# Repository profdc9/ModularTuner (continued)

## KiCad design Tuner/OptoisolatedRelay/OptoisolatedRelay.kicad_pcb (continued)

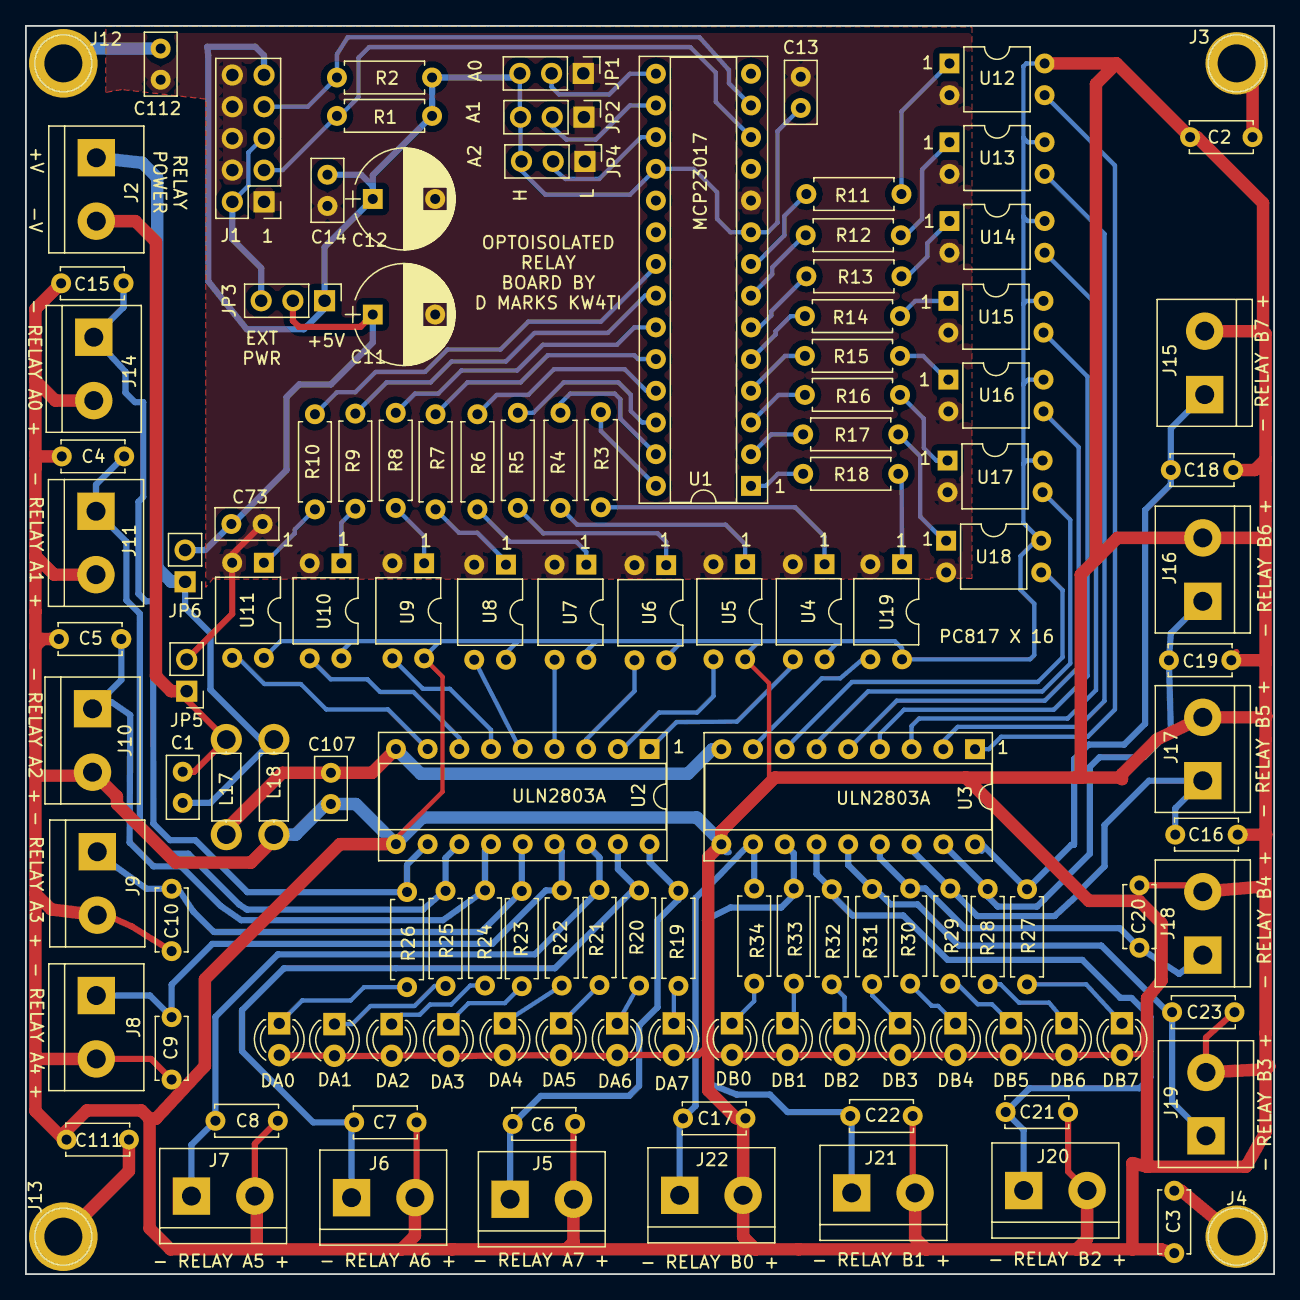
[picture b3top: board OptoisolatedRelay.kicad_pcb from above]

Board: 2 copper layers, 100.0 x 100.0 mm, 126 parts (0 on the bottom side), 97 nets.

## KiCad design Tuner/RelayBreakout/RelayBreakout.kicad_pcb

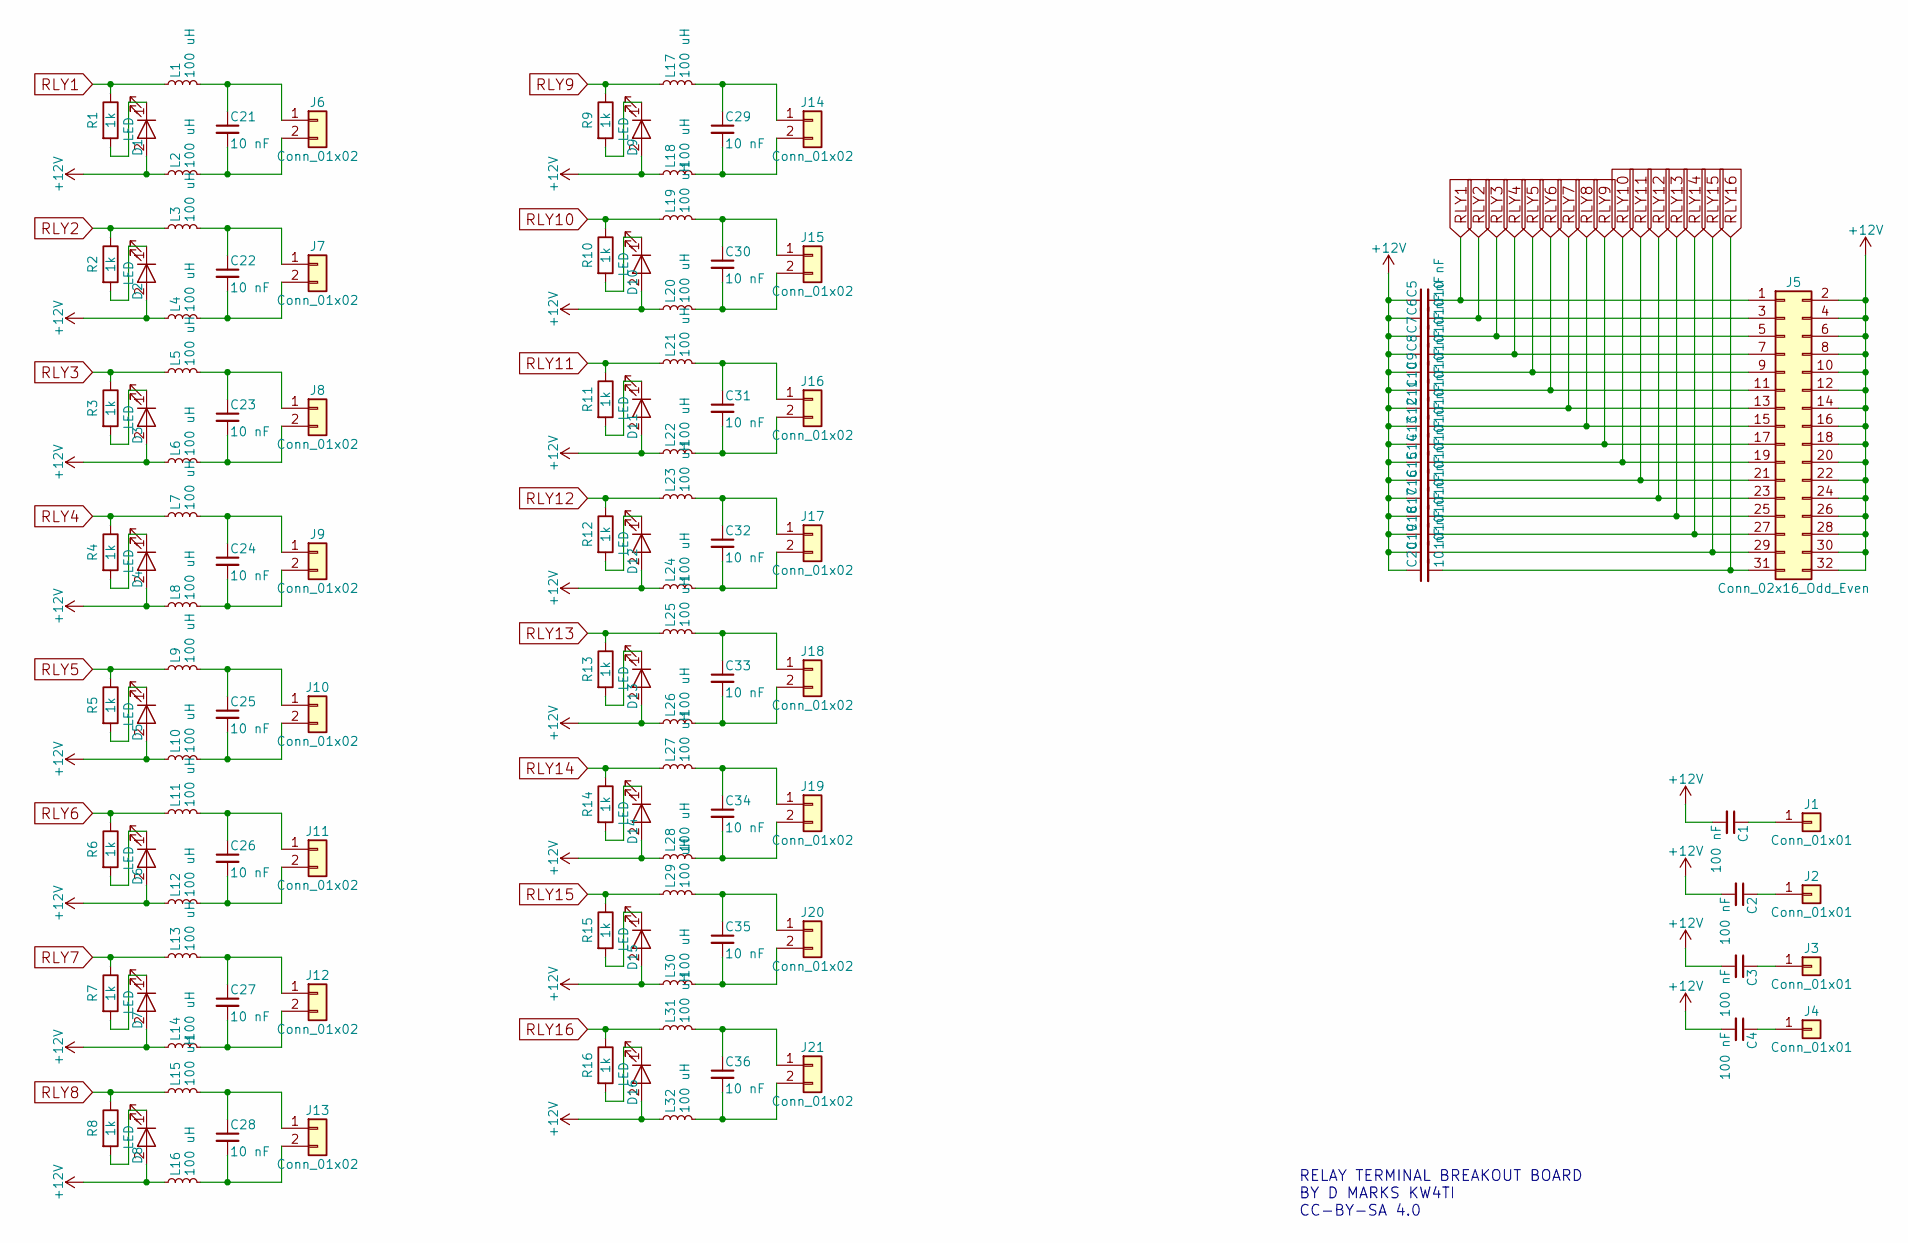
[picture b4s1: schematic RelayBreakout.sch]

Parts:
C1, C2, C3, C4: 100 nF; C_Disc_D5.0mm_W2.5mm_P5.00mm
C5, C6, C7, C8, C9, C10, C11, C12, C13, C14, C15, C16, C17, C18, C19, C20, C21, C22, C23, C24, C25, C26, C27, C28, C29, C30, C31, C32, C33, C34, C35, C36: 10 nF; C_Disc_D5.0mm_W2.5mm_P2.50mm
D1, D2, D3, D4, D5, D6, D7, D8, D9, D10, D11, D12, D13, D14, D15, D16: LED; LED_D3.0mm
J1, J2, J3, J4: Conn_01x01; 1pin
J5: Conn_02x16_Odd_Even; Pin_Header_Straight_2x16_Pitch2.54mm
J6, J7, J8, J9, J10, J11, J12, J13, J14, J15, J16, J17, J18, J19, J20, J21: Conn_01x02; TerminalBlock_bornier-2_P5.08mm
L1, L2, L3, L4, L5, L6, L7, L8, L9, L10, L11, L12, L13, L14, L15, L16, L17, L18, L19, L20, L21, L22, L23, L24, L25, L26, L27, L28, L29, L30, L31, L32: 100 uH; L_Axial_L5.3mm_D2.2mm_P7.62mm_Horizontal_Vishay_IM-1
R1, R2, R3, R4, R5, R6, R7, R8, R9, R10, R11, R12, R13, R14, R15, R16: 1k; R_Axial_DIN0207_L6.3mm_D2.5mm_P7.62mm_Horizontal

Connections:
+12V: C1.2, C2.2, C3.2, C4.2, C5.1, C6.1, C7.1, C8.1, C9.1, C10.1, C11.1, C12.1, C13.1, C14.1, C15.1, C16.1, C17.1, C18.1, C19.1, C20.1, D1.2 (A), D2.2 (A), D3.2 (A), D4.2 (A), D5.2 (A), D6.2 (A), D7.2 (A), D8.2 (A), D9.2 (A), D10.2 (A), D11.2 (A), D12.2 (A), D13.2 (A), D14.2 (A), D15.2 (A), D16.2 (A), J5.2, J5.4, J5.6, J5.8, J5.10, J5.12, J5.14, J5.16, J5.18, J5.20, J5.22, J5.24, J5.26, J5.28, J5.30, J5.32, L2.1, L4.1, L6.1, L8.1, L10.1, L12.1, L14.1, L16.1, L18.1, L20.1, L22.1, L24.1, L26.1, L28.1, L30.1, L32.1
unnamed: C1.1, J1.1
unnamed: C2.1, J2.1
unnamed: C3.1, J3.1
unnamed: C4.1, J4.1
unnamed: C21.1, J6.1, L1.2
unnamed: C21.2, J6.2, L2.2
unnamed: C22.1, J7.1, L3.2
unnamed: C22.2, J7.2, L4.2
unnamed: C23.1, J8.1, L5.2
unnamed: C23.2, J8.2, L6.2
unnamed: C24.1, J9.1, L7.2
unnamed: C24.2, J9.2, L8.2
unnamed: C25.1, J10.1, L9.2
unnamed: C25.2, J10.2, L10.2
unnamed: C26.1, J11.1, L11.2
unnamed: C26.2, J11.2, L12.2
unnamed: C27.1, J12.1, L13.2
unnamed: C27.2, J12.2, L14.2
unnamed: C28.1, J13.1, L15.2
unnamed: C28.2, J13.2, L16.2
unnamed: C29.1, J14.1, L17.2
unnamed: C29.2, J14.2, L18.2
unnamed: C30.1, J15.1, L19.2
unnamed: C30.2, J15.2, L20.2
unnamed: C31.1, J16.1, L21.2
unnamed: C31.2, J16.2, L22.2
unnamed: C32.1, J17.1, L23.2
unnamed: C32.2, J17.2, L24.2
unnamed: C33.1, J18.1, L25.2
unnamed: C33.2, J18.2, L26.2
unnamed: C34.1, J19.1, L27.2
unnamed: C34.2, J19.2, L28.2
unnamed: C35.1, J20.1, L29.2
unnamed: C35.2, J20.2, L30.2
unnamed: C36.1, J21.1, L31.2
unnamed: C36.2, J21.2, L32.2
unnamed: D1.1 (K), R1.2
unnamed: D2.1 (K), R2.2
unnamed: D3.1 (K), R3.2
unnamed: D4.1 (K), R4.2
unnamed: D5.1 (K), R5.2
unnamed: D6.1 (K), R6.2
unnamed: D7.1 (K), R7.2
unnamed: D8.1 (K), R8.2
unnamed: D9.1 (K), R9.2
unnamed: D10.1 (K), R10.2
unnamed: D11.1 (K), R11.2
unnamed: D12.1 (K), R12.2
unnamed: D13.1 (K), R13.2
unnamed: D14.1 (K), R14.2
unnamed: D15.1 (K), R15.2
unnamed: D16.1 (K), R16.2
RLY1: C5.2, J5.1, L1.1, R1.1
RLY2: C6.2, J5.3, L3.1, R2.1
RLY3: C7.2, J5.5, L5.1, R3.1
RLY4: C8.2, J5.7, L7.1, R4.1
RLY5: C9.2, J5.9, L9.1, R5.1
RLY6: C10.2, J5.11, L11.1, R6.1
RLY7: C11.2, J5.13, L13.1, R7.1
RLY8: C12.2, J5.15, L15.1, R8.1
RLY9: C13.2, J5.17, L17.1, R9.1
RLY10: C14.2, J5.19, L19.1, R10.1
RLY11: C15.2, J5.21, L21.1, R11.1
RLY12: C16.2, J5.23, L23.1, R12.1
RLY13: C17.2, J5.25, L25.1, R13.1
RLY14: C18.2, J5.27, L27.1, R14.1
RLY15: C19.2, J5.29, L29.1, R15.1
RLY16: C20.2, J5.31, L31.1, R16.1

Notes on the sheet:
RELAY TERMINAL BREAKOUT BOARD BY D MARKS KW4TI CC-BY-SA 4.0

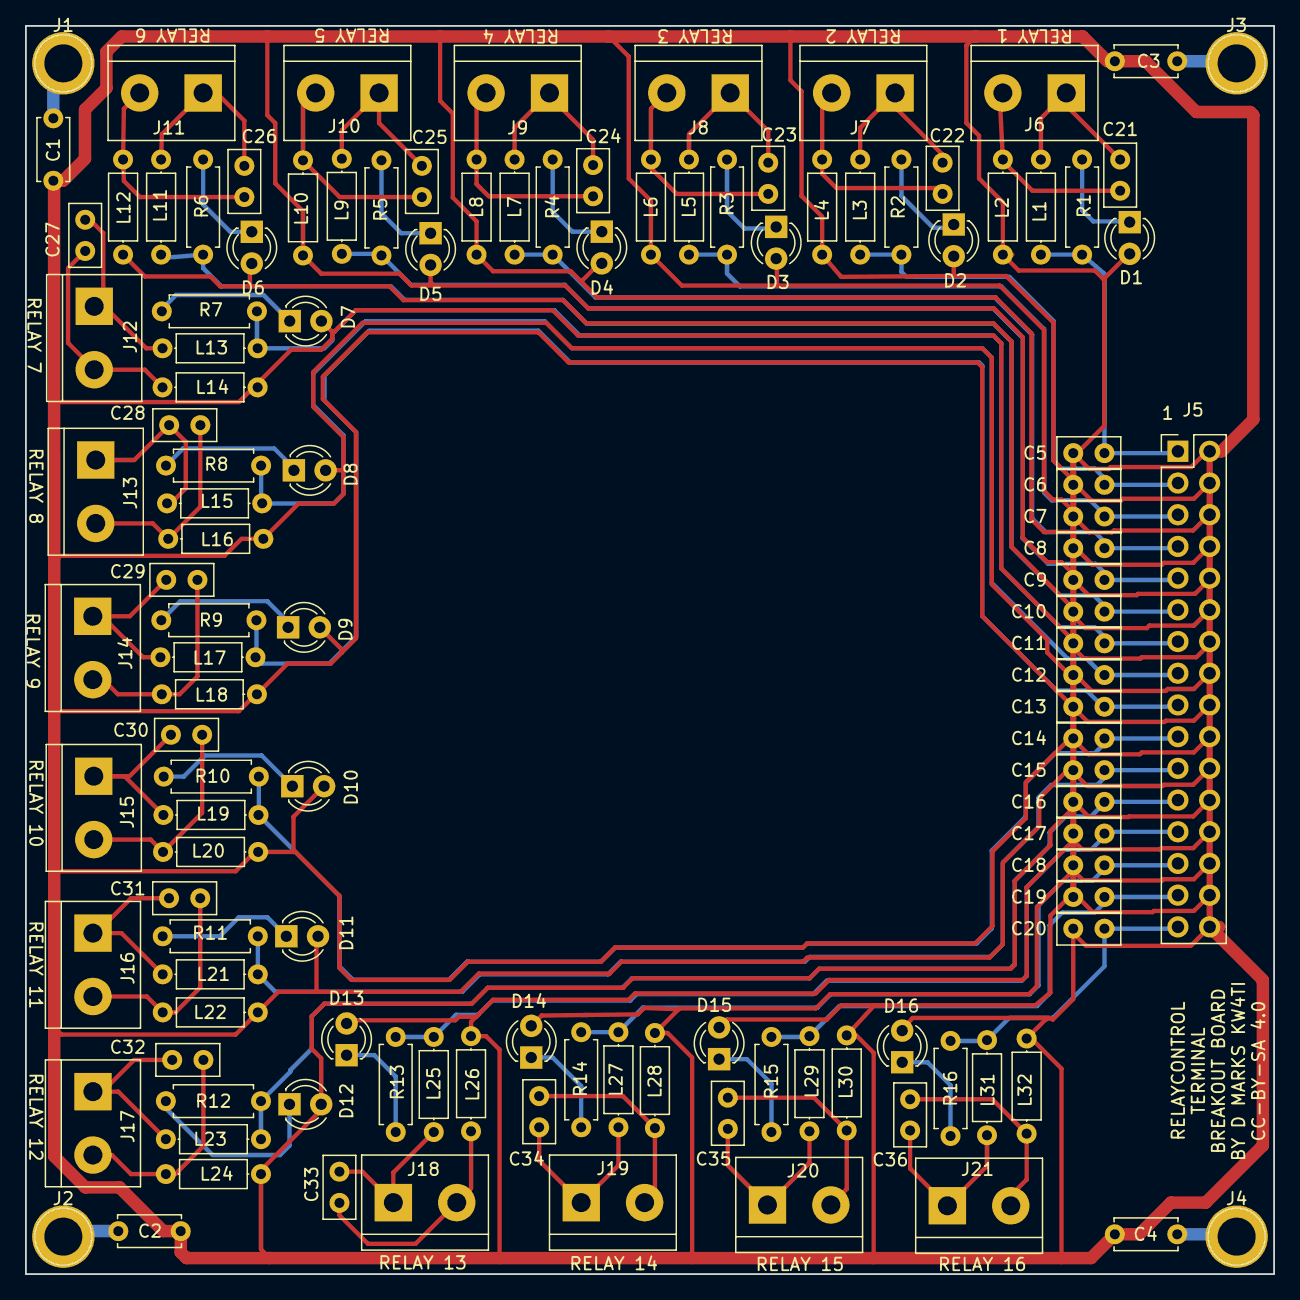
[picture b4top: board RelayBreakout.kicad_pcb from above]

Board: 2 copper layers, 100.0 x 100.0 mm, 121 parts (0 on the bottom side), 69 nets.

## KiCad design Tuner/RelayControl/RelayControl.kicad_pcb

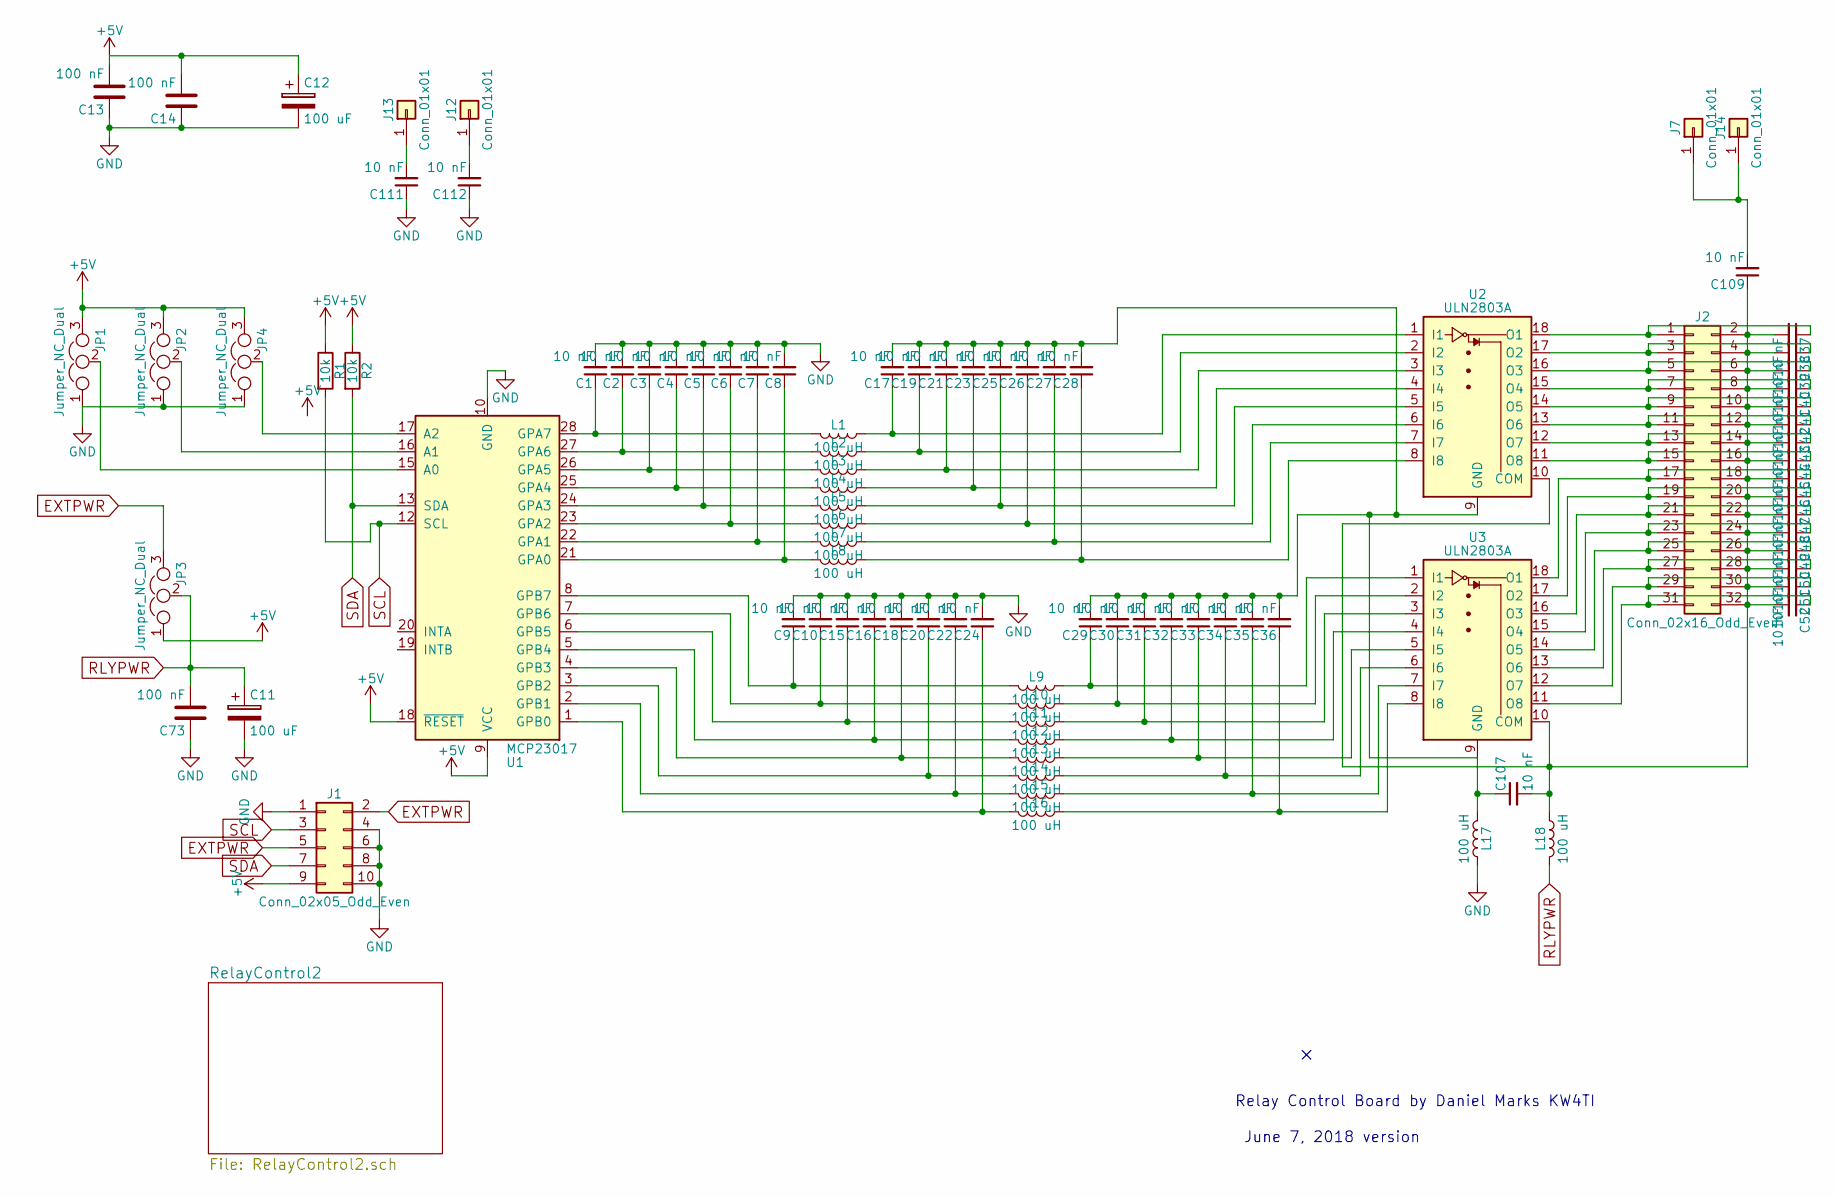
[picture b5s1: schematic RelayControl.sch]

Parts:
C1, C2, C3, C4, C5, C6, C7, C8, C9, C10, C15, C16, C17, C18, C19, C20, C21, C22, C23, C24, C25, C26, C27, C28, C29, C30, C31, C32, C33, C34, C35, C36, C37, C38, C39, C40, C41, C42, C43, C44, C45, C46, C47, C48, C49, C50, C51, C52, C107, C109, C111, C112: 10 nF; C_Disc_D5.0mm_W2.5mm_P2.50mm
C11, C12: 100 uF; CP_Radial_D8.0mm_P5.00mm
C13, C14, C73: 100 nF; C_Disc_D5.0mm_W2.5mm_P2.50mm
J1: Conn_02x05_Odd_Even; Pin_Header_Straight_2x05_Pitch2.54mm
J2: Conn_02x16_Odd_Even; Pin_Header_Straight_2x16_Pitch2.54mm
J7, J12, J13, J14: Conn_01x01; 1pin
JP1, JP2, JP3, JP4: Jumper_NC_Dual; Pin_Header_Straight_1x03_Pitch2.54mm
L1, L2, L3, L4, L5, L6, L7, L8, L9, L10, L11, L12, L13, L14, L15, L16, L17, L18: 100 uH; L_Axial_L5.3mm_D2.2mm_P7.62mm_Horizontal_Vishay_IM-1
R1, R2: 10k; R_Axial_DIN0207_L6.3mm_D2.5mm_P7.62mm_Horizontal
U1: MCP23017; DIP-28_W7.62mm_Socket
U2, U3: ULN2803A; DIP-18_W7.62mm_Socket

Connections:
+5V: C12.1, C13.2, C14.2, J1.9, JP1.3, JP2.3, JP3.1, JP4.3, R1.1, R2.1, U1.9 (VCC), U1.18 (~RESET); also elsewhere on the board
EXTPWR: J1.2, J1.5, JP3.3; also elsewhere on the board
GND: C1.2, C2.2, C3.2, C4.2, C5.2, C6.2, C7.2, C8.2, C9.2, C10.2, C11.2, C12.2, C13.1, C14.1, C15.2, C16.2, C18.2, C20.2, C22.2, C24.2, C73.1, C111.1, C112.1, J1.1, J1.4, J1.6, J1.8, J1.10, JP1.1, JP2.1, JP4.1, L17.1, U1.10 (GND); also elsewhere on the board
unnamed: C1.1, L1.2, U1.28 (GPA7)
unnamed: C2.1, L2.2, U1.27 (GPA6)
unnamed: C3.1, L3.2, U1.26 (GPA5)
unnamed: C4.1, L4.2, U1.25 (GPA4)
unnamed: C5.1, L5.2, U1.24 (GPA3)
unnamed: C6.1, L6.2, U1.23 (GPA2)
unnamed: C7.1, L7.2, U1.22 (GPA1)
unnamed: C8.1, L8.2, U1.21 (GPA0)
unnamed: C9.1, L9.2, U1.8 (GPB7)
unnamed: C10.1, L10.2, U1.7 (GPB6)
unnamed: C15.1, L11.2, U1.6 (GPB5)
unnamed: C16.1, L12.2, U1.5 (GPB4)
unnamed: C17.1, L1.1, U2.1 (I1)
unnamed: C18.1, L13.2, U1.4 (GPB3)
unnamed: C19.1, L2.1, U2.2 (I2)
unnamed: C20.1, L14.2, U1.3 (GPB2)
unnamed: C21.1, L3.1, U2.3 (I3)
unnamed: C22.1, L15.2, U1.2 (GPB1)
unnamed: C23.1, L4.1, U2.4 (I4)
unnamed: C24.1, L16.2, U1.1 (GPB0)
unnamed: C25.1, L5.1, U2.5 (I5)
unnamed: C26.1, L6.1, U2.6 (I6)
unnamed: C27.1, L7.1, U2.7 (I7)
unnamed: C28.1, L8.1, U2.8 (I8)
unnamed: C29.1, L9.1, U3.1 (I1)
unnamed: C30.1, L10.1, U3.2 (I2)
unnamed: C31.1, L11.1, U3.3 (I3)
unnamed: C32.1, L12.1, U3.4 (I4)
unnamed: C33.1, L13.1, U3.5 (I5)
unnamed: C34.1, L14.1, U3.6 (I6)
unnamed: C35.1, L15.1, U3.7 (I7)
unnamed: C36.1, L16.1, U3.8 (I8)
unnamed: C37.1, J2.1, U2.18 (O1)
unnamed: C38.1, J2.3, U2.17 (O2)
unnamed: C39.1, J2.5, U2.16 (O3)
unnamed: C40.1, J2.7, U2.15 (O4)
unnamed: C41.1, J2.9, U2.14 (O5)
unnamed: C42.1, J2.11, U2.13 (O6)
unnamed: C43.1, J2.13, U2.12 (O7)
unnamed: C44.1, J2.15, U2.11 (O8)
unnamed: C45.1, J2.17, U3.18 (O1)
unnamed: C46.1, J2.19, U3.17 (O2)
unnamed: C47.1, J2.21, U3.16 (O3)
unnamed: C48.1, J2.23, U3.15 (O4)
unnamed: C49.1, J2.25, U3.14 (O5)
unnamed: C50.1, J2.27, U3.13 (O6)
unnamed: C51.1, J2.29, U3.12 (O7)
unnamed: C52.1, J2.31, U3.11 (O8)
unnamed: C17.2, C19.2, C21.2, C23.2, C25.2, C26.2, C27.2, C28.2, C29.2, C30.2, C31.2, C32.2, C33.2, C34.2, C35.2, C36.2, C107.1, L17.2, U2.9 (GND), U3.9 (GND)
unnamed: C37.2, C38.2, C39.2, C40.2, C41.2, C42.2, C43.2, C44.2, C45.2, C46.2, C47.2, C48.2, C49.2, C50.2, C51.2, C52.2, C107.2, C109.1, J2.2, J2.4, J2.6, J2.8, J2.10, J2.12, J2.14, J2.16, J2.18, J2.20, J2.22, J2.24, J2.26, J2.28, J2.30, J2.32, L18.1, U2.10 (COM), U3.10 (COM)
unnamed: C109.2, J7.1, J14.1
unnamed: C111.2, J13.1
unnamed: C112.2, J12.1
unnamed: JP1.2, U1.15 (A0)
unnamed: JP2.2, U1.16 (A1)
unnamed: JP4.2, U1.17 (A2)
RLYPWR: C11.1, C73.2, JP3.2, L18.2
SCL: J1.3, R1.2, U1.12 (SCL); also elsewhere on the board
SDA: J1.7, R2.2, U1.13 (SDA); also elsewhere on the board

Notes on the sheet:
Relay Control Board by Daniel Marks KW4TI
June 7, 2018 version

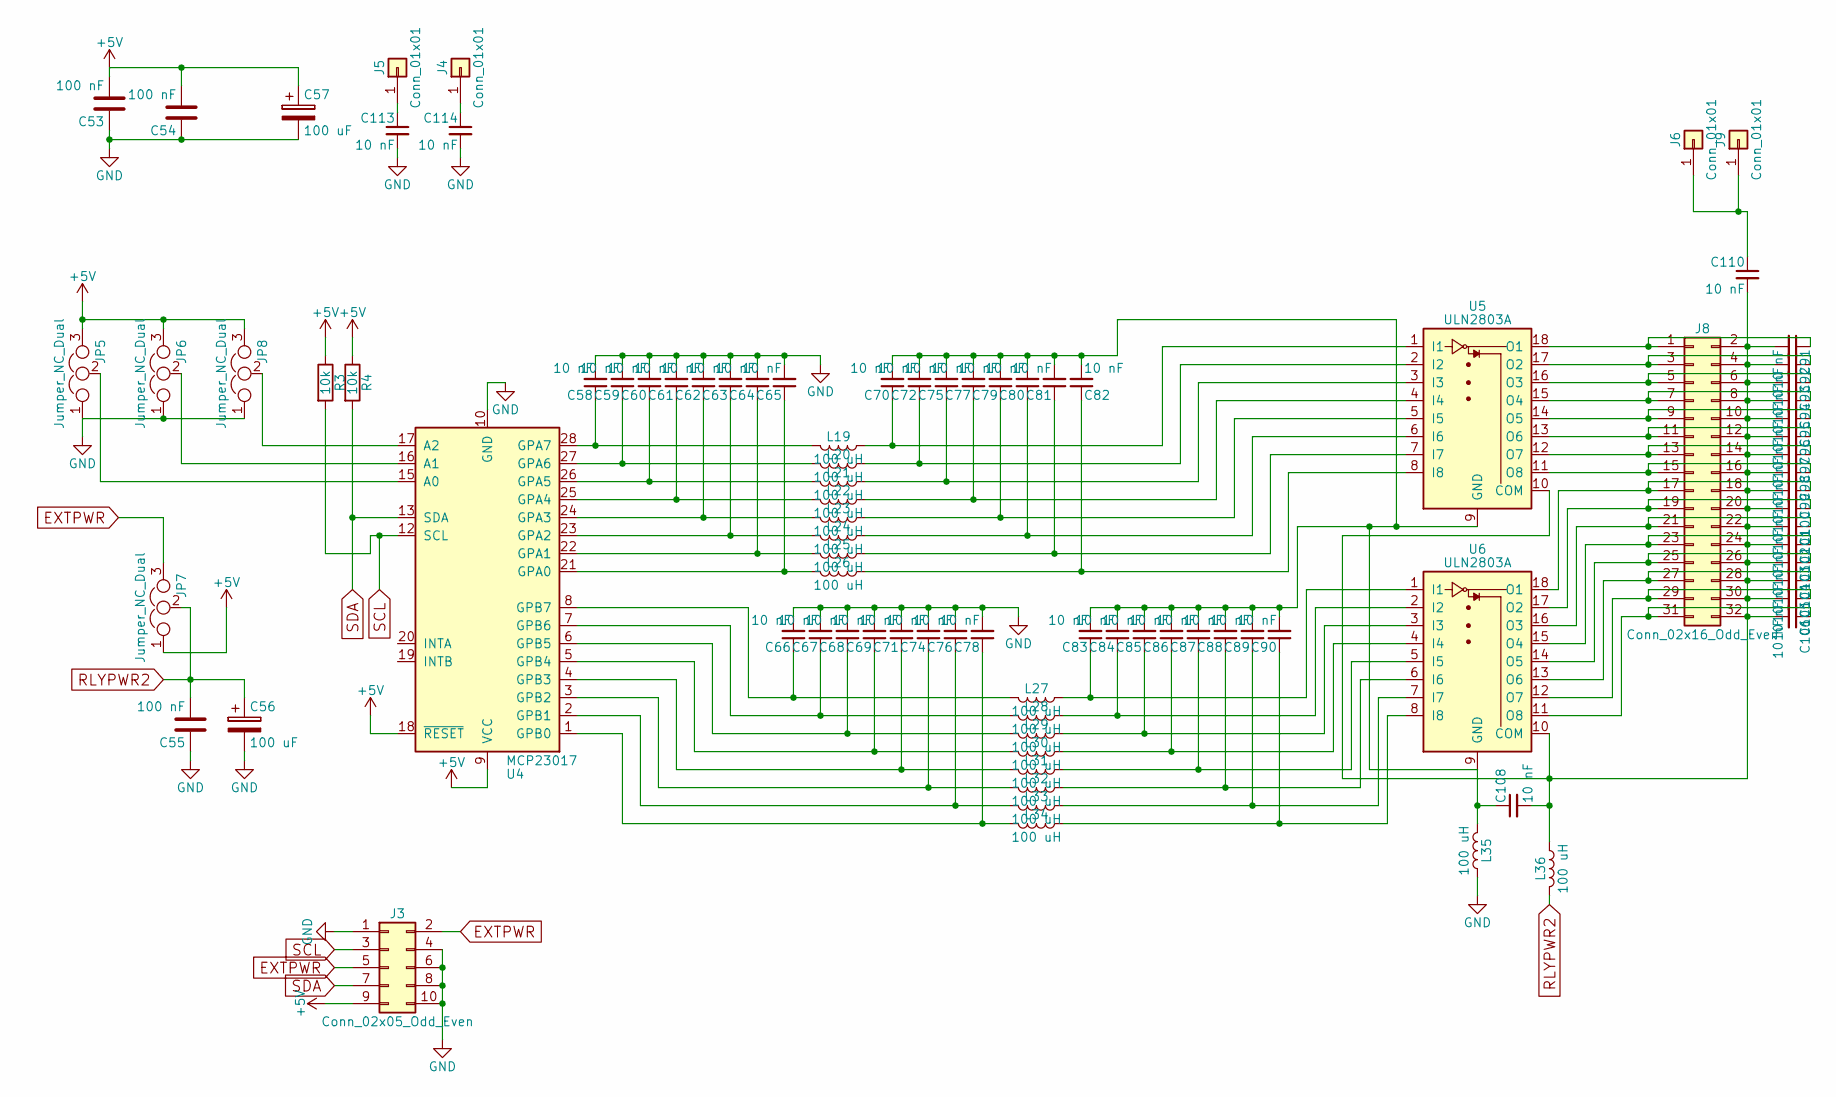
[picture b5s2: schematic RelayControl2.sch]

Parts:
C53, C54, C55: 100 nF; C_Disc_D5.0mm_W2.5mm_P2.50mm
C56, C57: 100 uF; CP_Radial_D8.0mm_P5.00mm
C58, C59, C60, C61, C62, C63, C64, C65, C66, C67, C68, C69, C70, C71, C72, C74, C75, C76, C77, C78, C79, C80, C81, C82, C83, C84, C85, C86, C87, C88, C89, C90, C91, C92, C93, C94, C95, C96, C97, C98, C99, C100, C101, C102, C103, C104, C105, C106, C108, C110, C113, C114: 10 nF; C_Disc_D5.0mm_W2.5mm_P2.50mm
J3: Conn_02x05_Odd_Even; Pin_Header_Straight_2x05_Pitch2.54mm
J4, J5, J6, J9: Conn_01x01; 1pin
J8: Conn_02x16_Odd_Even; Pin_Header_Straight_2x16_Pitch2.54mm
JP5, JP6, JP7, JP8: Jumper_NC_Dual; Pin_Header_Straight_1x03_Pitch2.54mm
L19, L20, L21, L22, L23, L24, L25, L26, L27, L28, L29, L30, L31, L32, L33, L34, L35, L36: 100 uH; L_Axial_L5.3mm_D2.2mm_P7.62mm_Horizontal_Vishay_IM-1
R3, R4: 10k; R_Axial_DIN0207_L6.3mm_D2.5mm_P7.62mm_Horizontal
U4: MCP23017; DIP-28_W7.62mm_Socket
U5, U6: ULN2803A; DIP-18_W7.62mm_Socket

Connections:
+5V: C53.2, C54.2, C57.1, J3.9, JP5.3, JP6.3, JP7.1, JP8.3, R3.1, R4.1, U4.9 (VCC), U4.18 (~RESET); also elsewhere on the board
EXTPWR: J3.2, J3.5, JP7.3; also elsewhere on the board
GND: C53.1, C54.1, C55.1, C56.2, C57.2, C58.2, C59.2, C60.2, C61.2, C62.2, C63.2, C64.2, C65.2, C66.2, C67.2, C68.2, C69.2, C71.2, C74.2, C76.2, C78.2, C113.2, C114.2, J3.1, J3.4, J3.6, J3.8, J3.10, JP5.1, JP6.1, JP8.1, L35.1, U4.10 (GND); also elsewhere on the board
unnamed: C58.1, L19.2, U4.28 (GPA7)
unnamed: C59.1, L20.2, U4.27 (GPA6)
unnamed: C60.1, L21.2, U4.26 (GPA5)
unnamed: C61.1, L22.2, U4.25 (GPA4)
unnamed: C62.1, L23.2, U4.24 (GPA3)
unnamed: C63.1, L24.2, U4.23 (GPA2)
unnamed: C64.1, L25.2, U4.22 (GPA1)
unnamed: C65.1, L26.2, U4.21 (GPA0)
unnamed: C66.1, L27.2, U4.8 (GPB7)
unnamed: C67.1, L28.2, U4.7 (GPB6)
unnamed: C68.1, L29.2, U4.6 (GPB5)
unnamed: C69.1, L30.2, U4.5 (GPB4)
unnamed: C70.1, L19.1, U5.1 (I1)
unnamed: C71.1, L31.2, U4.4 (GPB3)
unnamed: C72.1, L20.1, U5.2 (I2)
unnamed: C74.1, L32.2, U4.3 (GPB2)
unnamed: C75.1, L21.1, U5.3 (I3)
unnamed: C76.1, L33.2, U4.2 (GPB1)
unnamed: C77.1, L22.1, U5.4 (I4)
unnamed: C78.1, L34.2, U4.1 (GPB0)
unnamed: C79.1, L23.1, U5.5 (I5)
unnamed: C80.1, L24.1, U5.6 (I6)
unnamed: C81.1, L25.1, U5.7 (I7)
unnamed: C82.1, L26.1, U5.8 (I8)
unnamed: C83.1, L27.1, U6.1 (I1)
unnamed: C84.1, L28.1, U6.2 (I2)
unnamed: C85.1, L29.1, U6.3 (I3)
unnamed: C86.1, L30.1, U6.4 (I4)
unnamed: C87.1, L31.1, U6.5 (I5)
unnamed: C88.1, L32.1, U6.6 (I6)
unnamed: C89.1, L33.1, U6.7 (I7)
unnamed: C90.1, L34.1, U6.8 (I8)
unnamed: C91.1, J8.1, U5.18 (O1)
unnamed: C92.1, J8.3, U5.17 (O2)
unnamed: C93.1, J8.5, U5.16 (O3)
unnamed: C94.1, J8.7, U5.15 (O4)
unnamed: C95.1, J8.9, U5.14 (O5)
unnamed: C96.1, J8.11, U5.13 (O6)
unnamed: C97.1, J8.13, U5.12 (O7)
unnamed: C98.1, J8.15, U5.11 (O8)
unnamed: C99.1, J8.17, U6.18 (O1)
unnamed: C100.1, J8.19, U6.17 (O2)
unnamed: C91.2, C92.2, C93.2, C94.2, C95.2, C96.2, C97.2, C98.2, C99.2, C100.2, C101.2, C102.2, C103.2, C104.2, C105.2, C106.2, C108.2, C110.2, J8.2, J8.4, J8.6, J8.8, J8.10, J8.12, J8.14, J8.16, J8.18, J8.20, J8.22, J8.24, J8.26, J8.28, J8.30, J8.32, L36.1, U5.10 (COM), U6.10 (COM)
unnamed: C101.1, J8.21, U6.16 (O3)
unnamed: C102.1, J8.23, U6.15 (O4)
unnamed: C103.1, J8.25, U6.14 (O5)
unnamed: C104.1, J8.27, U6.13 (O6)
unnamed: C105.1, J8.29, U6.12 (O7)
unnamed: C106.1, J8.31, U6.11 (O8)
unnamed: C70.2, C72.2, C75.2, C77.2, C79.2, C80.2, C81.2, C82.2, C83.2, C84.2, C85.2, C86.2, C87.2, C88.2, C89.2, C90.2, C108.1, L35.2, U5.9 (GND), U6.9 (GND)
unnamed: C110.1, J6.1, J9.1
unnamed: C113.1, J5.1
unnamed: C114.1, J4.1
unnamed: JP5.2, U4.15 (A0)
unnamed: JP6.2, U4.16 (A1)
unnamed: JP8.2, U4.17 (A2)
RLYPWR2: C55.2, C56.1, JP7.2, L36.2
SCL: J3.3, R3.2, U4.12 (SCL); also elsewhere on the board
SDA: J3.7, R4.2, U4.13 (SDA); also elsewhere on the board

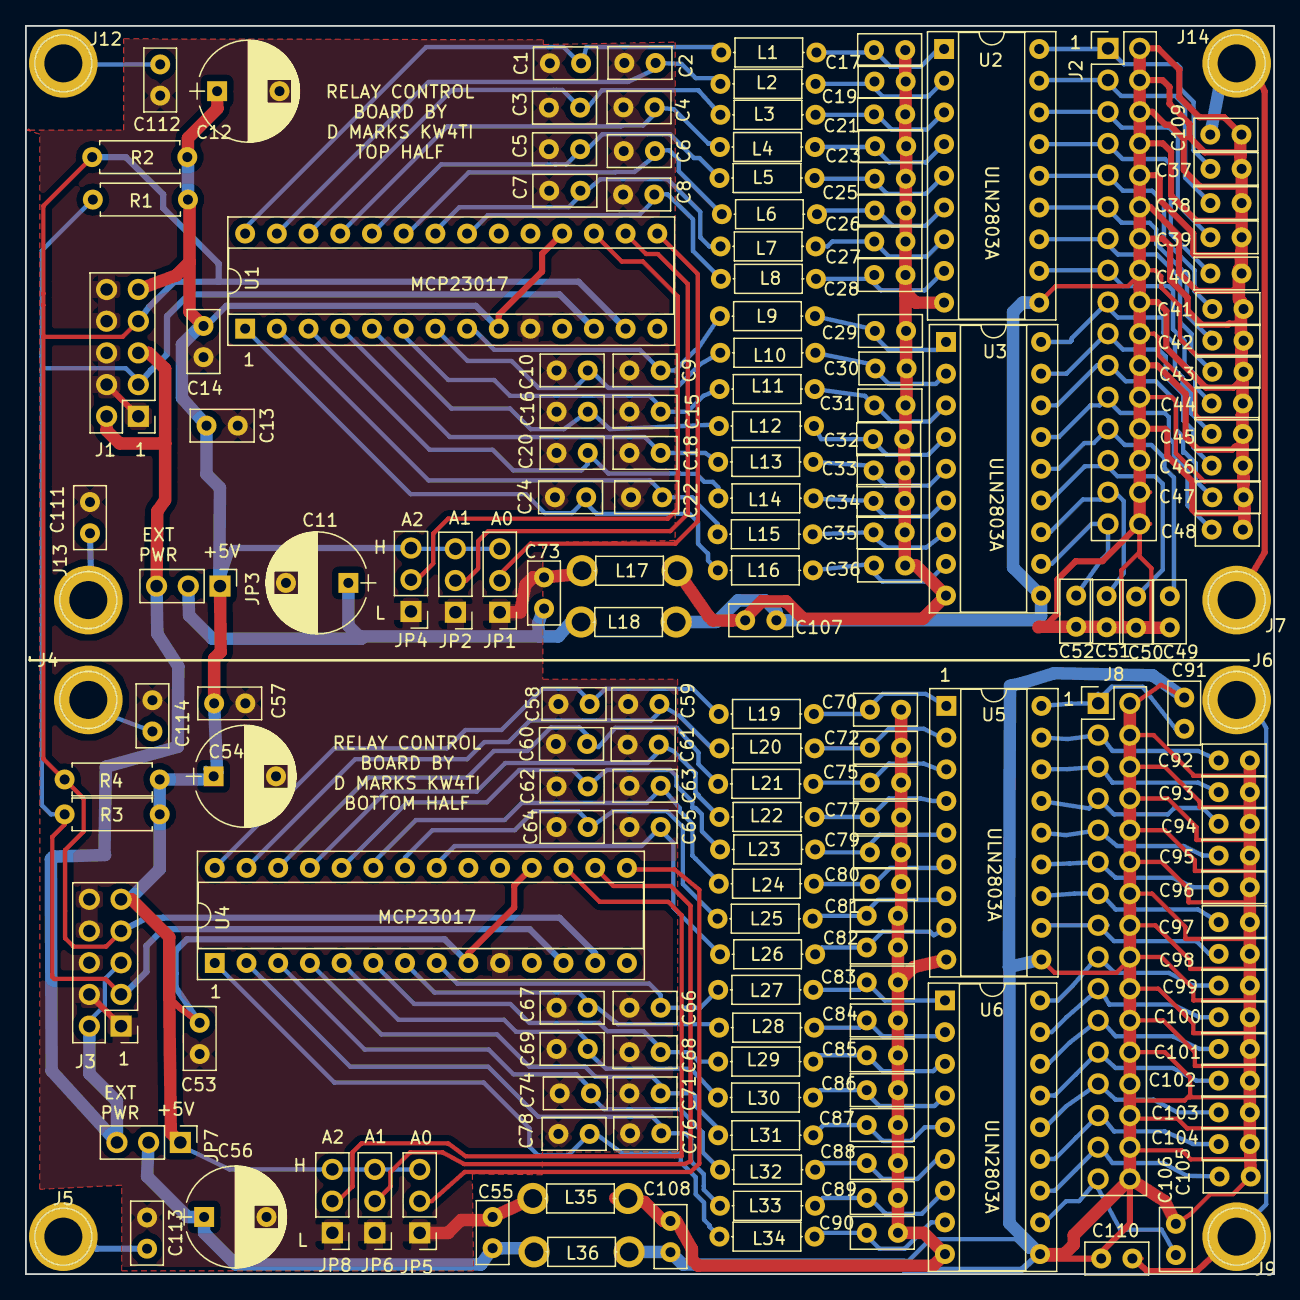
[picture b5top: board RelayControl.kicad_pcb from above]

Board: 2 copper layers, 100.0 x 100.0 mm, 180 parts (0 on the bottom side), 119 nets.

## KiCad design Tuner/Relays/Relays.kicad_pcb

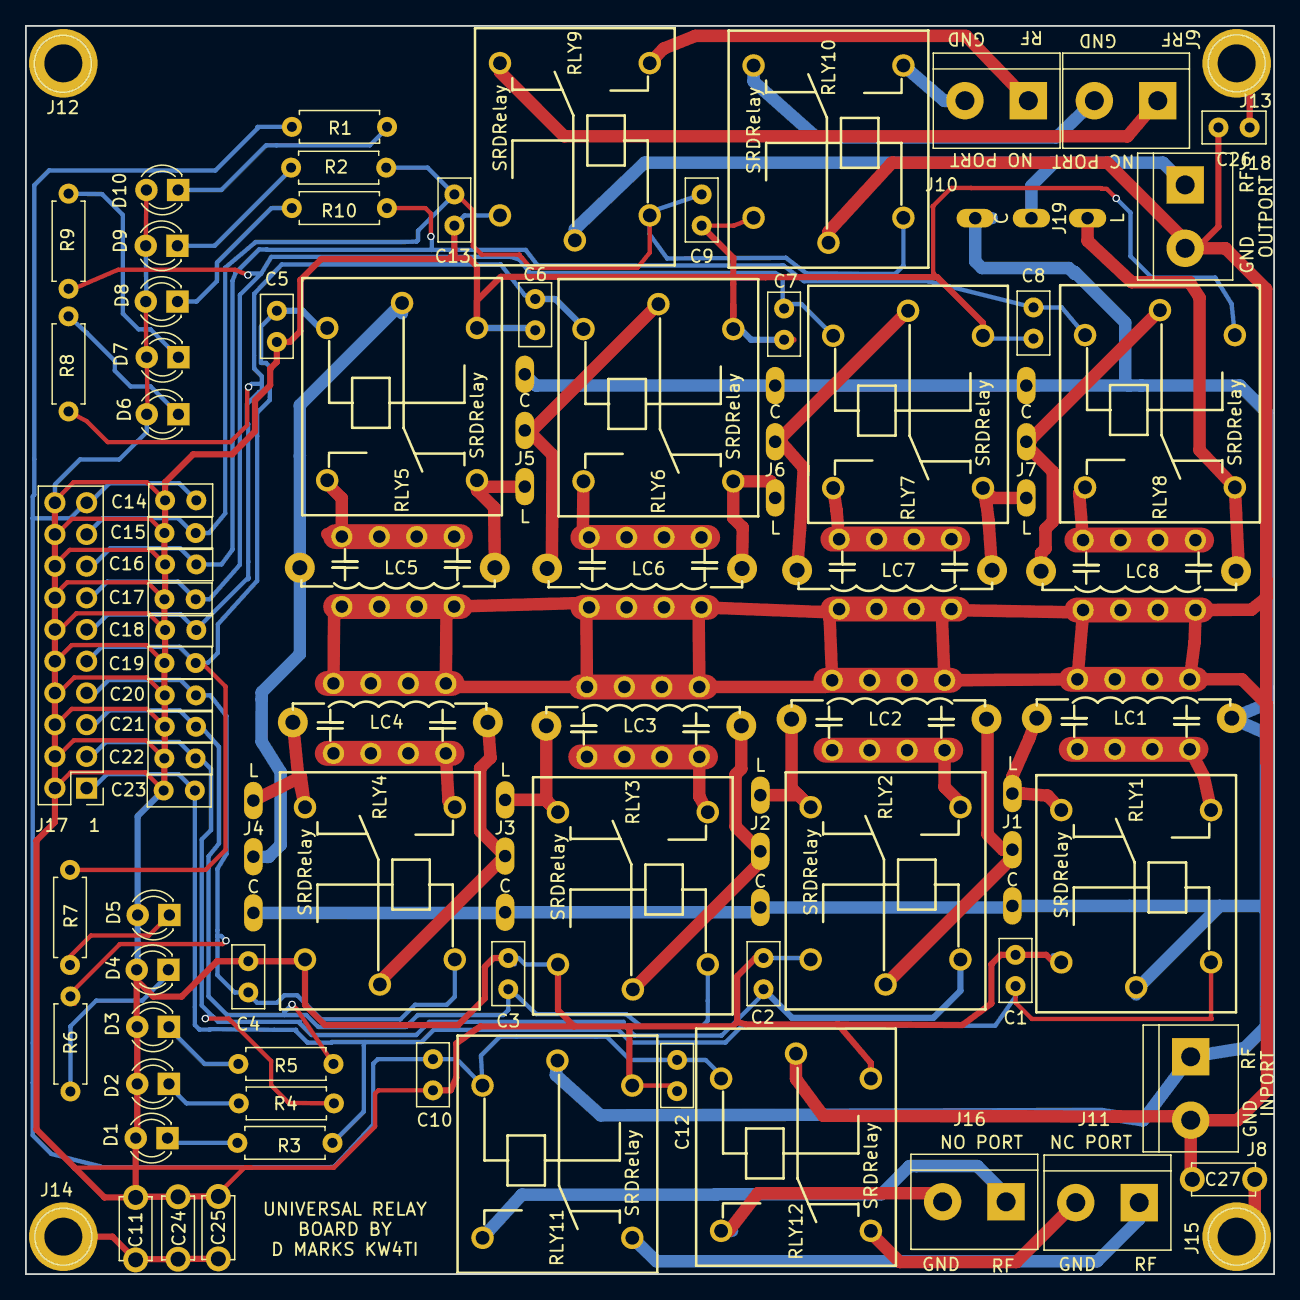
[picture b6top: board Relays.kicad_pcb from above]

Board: 2 copper layers, 100.0 x 100.0 mm, 86 parts (0 on the bottom side), 58 nets.

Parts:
C1, C2, C3, C4, C5, C6, C7, C8, C9, C10, C12, C13, C14, C15, C16, C17, C18, C19, C20, C21, C22, C23, C26: 10 nF; C_Disc_D5.0mm_W2.5mm_P2.50mm
C11, C24, C25, C27: 10 nF; C_Disc_D5.0mm_W2.5mm_P5.00mm
D1, D2, D3, D4, D5, D6, D7, D8, D9, D10: LED; LED_D3.0mm
J1, J2, J3, J4, J5, J6, J7, J19: Conn_01x03; ThreeJumperPt
J8, J9, J10, J11, J16, J18: Conn_01x02; TerminalBlock_bornier-2_P5.08mm
J12, J13, J14, J15: Conn_01x01; 1pin
J17: Conn_02x10_Odd_Even; Pin_Header_Straight_2x10_Pitch2.54mm
LC1, LC2, LC3, LC4, LC5, LC6, LC7, LC8: CAPIND; MultiCAPIND
R1, R2, R3, R4, R5, R6, R7, R8, R9, R10: 1k; R_Axial_DIN0207_L6.3mm_D2.5mm_P7.62mm_Horizontal
RLY1, RLY2, RLY3, RLY4, RLY5, RLY6, RLY7, RLY8, RLY9, RLY10, RLY11, RLY12: SPDTRelay; SRDXXRelay

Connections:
+5V: C1.2, C2.2, C3.2, C4.2, C5.2, C6.2, C7.2, C8.2, C9.2, C10.2, C11.2, C12.2, C13.2, C14.2, C15.2, C16.2, C17.2, C18.2, C19.2, C20.2, C21.2, C22.2, C23.2, C24.2, C25.2, D1.2, D2.2, D3.2, D4.2, D5.2, D6.2, D7.2, D8.2, D9.2, D10.2, J17.2, J17.4, J17.6, J17.8, J17.10, J17.12, J17.14, J17.16, J17.18, J17.20, RLY1.4, RLY2.4, RLY3.4, RLY4.4, RLY5.4, RLY6.4, RLY7.4, RLY8.4, RLY9.4, RLY10.4, RLY11.4, RLY12.4
unnamed: C11.1, C24.1, C25.1, J14.1
unnamed: C26.1, J13.1
unnamed: C27.1, J15.1
unnamed: D1.1, R3.1
unnamed: D2.1, R4.1
unnamed: D3.1, R5.1
unnamed: D4.1, R6.1
unnamed: D5.1, R7.1
unnamed: D6.1, R8.1
unnamed: D7.1, R9.1
unnamed: D8.1, R10.1
unnamed: D9.1, R2.1
unnamed: D10.1, R1.1
unnamed: J1.1, LC1.3, RLY1.2
unnamed: J1.2, LC2.4, RLY2.1
unnamed: J2.1, LC2.3, RLY2.2
unnamed: J2.2, LC3.4, RLY3.1
unnamed: J3.1, LC3.3, RLY3.2
unnamed: J3.2, LC4.4, RLY4.1
unnamed: J4.1, LC4.3, RLY4.2
unnamed: J4.2, LC5.4, RLY5.1
unnamed: J5.1, LC5.3, RLY5.2
unnamed: J5.2, LC6.4, RLY6.1
unnamed: J6.1, LC6.3, RLY6.2
unnamed: J6.2, LC7.4, RLY7.1
unnamed: J7.1, LC7.3, RLY7.2
unnamed: J7.2, LC8.4, RLY8.1
unnamed: J9.1, RLY9.2
unnamed: J9.2, RLY10.2
unnamed: J10.1, RLY9.3
unnamed: J10.2, RLY10.3
unnamed: J11.1, RLY11.2
unnamed: J11.2, RLY12.2
unnamed: J16.1, RLY11.3
unnamed: J16.2, RLY12.3
unnamed: J18.1, J19.2, RLY9.1
unnamed: J19.1, LC8.3, RLY8.2
unnamed: LC1.1, RLY1.3
unnamed: LC2.1, RLY2.3
unnamed: LC3.1, RLY3.3
unnamed: LC4.1, RLY4.3
unnamed: LC5.1, RLY5.3
unnamed: LC6.1, RLY6.3
unnamed: LC7.1, RLY7.3
unnamed: LC8.1, RLY8.3
RFGND: C26.2, C27.2, J8.2, J18.2, LC1.2, LC2.2, LC3.2, LC4.2, LC5.2, LC6.2, LC7.2, LC8.2, RLY10.1, RLY12.1
RFSIG: J1.3, J2.3, J3.3, J4.3, J5.3, J6.3, J7.3, J8.1, J19.3, LC1.4, RLY1.1, RLY11.1
RLY1: C1.1, C23.1, J17.1, R3.2, RLY1.5
RLY2: C2.1, C22.1, J17.3, R4.2, RLY2.5
RLY3: C3.1, C21.1, J17.5, R5.2, RLY3.5
RLY4: C4.1, C20.1, J17.7, R6.2, RLY4.5
RLY5: C5.1, C19.1, J17.9, R7.2, RLY5.5
RLY6: C6.1, C18.1, J17.11, R8.2, RLY6.5
RLY7: C7.1, C17.1, J17.13, R9.2, RLY7.5
RLY8: C8.1, C16.1, J17.15, R10.2, RLY8.5
RLY9: C9.1, C13.1, C15.1, J17.17, R2.2, RLY9.5, RLY10.5
RLY10: C10.1, C12.1, C14.1, J17.19, R1.2, RLY11.5, RLY12.5
